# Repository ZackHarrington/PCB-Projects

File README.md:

# PCB Projects
This repository holds all my personal Autodesk Eagle (now Fusion 360 and KiCAD) projects and libraries

__Projects:__
- Billy Bass Board: 	A board to convert or 'hack' a Big Mouth Billy Bass into an IoT device - in progress
- Christmas Snow Globe:	A board using an ATtiny85 as a 6-hour timer IC in a custom snow globe - made as a gift
- Greek Keyboard:	A 5x6 key keyboard using an ATmega32u4 and HID to input Greek Unicode - made as a gift
- LED Test Board:	A simple board for testing any combination of LED, resistor, and power source
- USB UART Board:	Two small boards for programming ESP32 modules, each for a different USB-to-UART IC

__Libraries:__
- Aesthetics:	Silkscreen and copper designs
- Capacitors: 	SEM (Samsung Electro-Mechanics) MLCC capacitors
- Connectors: 	Board inputs or outputs
- Diodes:	Standard and Schottky diodes with Kingbright LEDs
- Energy:	Batteries and energy storage
- ICs: 		Integrates circuits
- Inductors:	SEM (Samsung Electro-Mechanics) Power Inductors
- Oscillators:	Crystal Oscillators
- Resistors:	SEM (Samsung Electro-Mechanics) CHIP-R chip resistors and potentiometers
- Switches: 	Physical buttons and switches
- Symbols:	Schematic symbols
- Transistors:	Discrete MOSFETs and BJTs

__Design Blocks:__
- ESP32 Wrover Module:	All standard capacitors and connections for implementing an ESP32-WROVER module

Note: I'm still in the process of finalizing the documentation for each project

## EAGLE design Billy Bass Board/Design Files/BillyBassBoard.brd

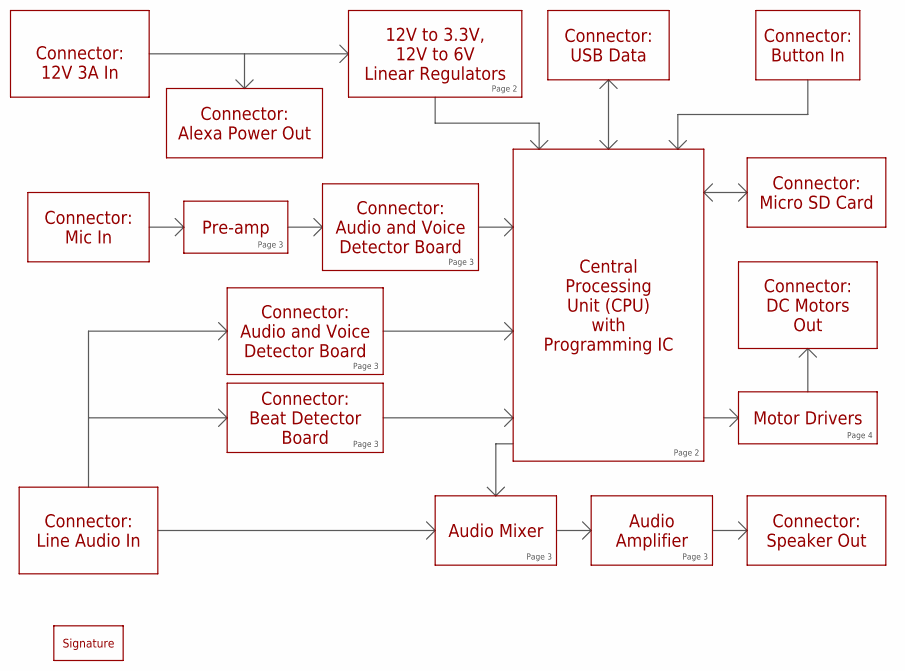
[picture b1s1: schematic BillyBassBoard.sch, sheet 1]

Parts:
U$122: SIGNATURE

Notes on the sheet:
Central Processing Unit (CPU) with Programming IC
Connector: 12V 3A In
Connector: Line Audio In
Connector: Speaker Out
Connector: DC Motors Out
12V to 3.3V, 12V to 6V Linear Regulators
Motor Drivers
Audio Mixer
Audio Amplifier
Page 2
Page 4
Page 3
Connector: Micro SD Card
Connector: Button In
Connector: USB Data
Connector: Alexa Power Out
Connector: Beat Detector Board
Connector: Audio and Voice Detector Board
Connector: Mic In
Pre-amp

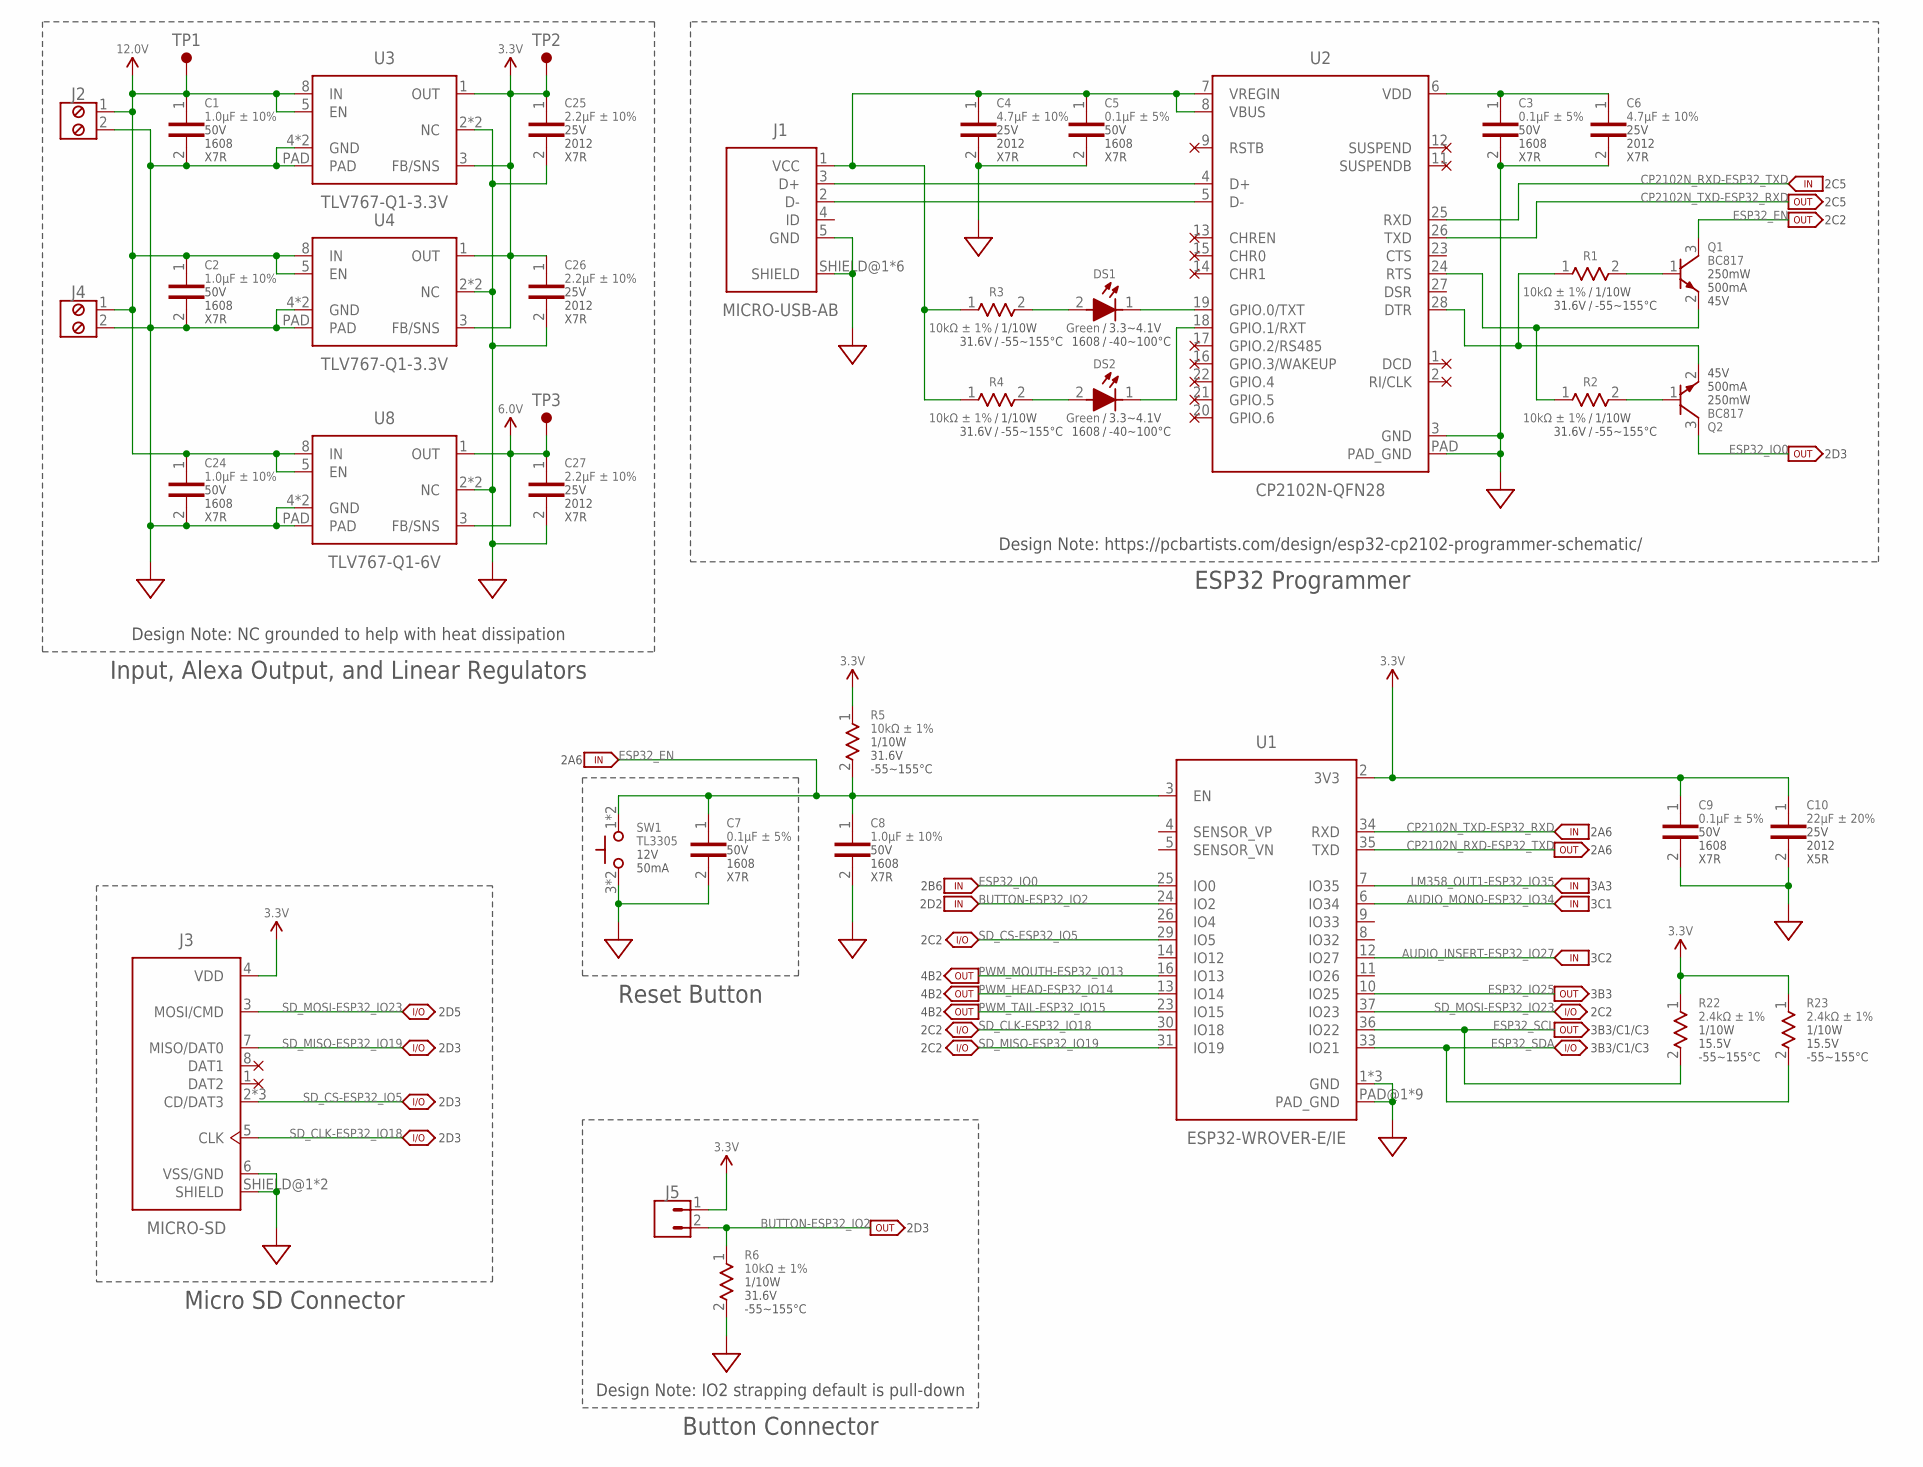
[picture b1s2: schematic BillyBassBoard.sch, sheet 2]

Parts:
C1, C2, C8, C24: 1.0µF ± 10%; 1608-SEM
C3, C5, C7, C9: 0.1µF ± 5%; 1608-SEM
C4, C6: 4.7µF ± 10%; 2012-SEM
C10: 22µF ± 20%; 2012-SEM
C25, C26, C27: 2.2µF ± 10%; 2012-SEM
DS1, DS2: Green; 1608
J1: MICRO-USB-AB; 47589-0001
J2, J4: MPT-2-SCREW; MPT-0.5/2-2.54
J3: MICRO-SD; MEM2061
J5: JST-XH-2; B2B-XH-A
Q1, Q2: BC817; SOT-23
R1, R2, R3, R4, R5, R6: 10kΩ ± 1%; 1608-SEM
R22, R23: 2.4kΩ ± 1%; 1608-SEM
SW1: TL3305
TP1, TP2, TP3: TEST-POINT
U1: ESP32-WROVER-E/IE
U2: CP2102N-QFN28; QFN28
U3, U4: TLV767-Q1-3.3V; VSON
U8: TLV767-Q1-6V; VSON

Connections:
3.3V: C9.1, C10.1, C25.1, C26.1, J3.4 (VDD), J5.1, R5.1, R22.1, R23.1, TP2.TP, U1.2 (3V3), U3.1 (OUT), U3.3 (FB/SNS), U4.1 (OUT), U4.3 (FB/SNS); also elsewhere on the board
6.0V: C27.1, TP3.TP, U8.1 (OUT), U8.3 (FB/SNS); also elsewhere on the board
12.0V: C1.1, C2.1, C24.1, J2.1, J4.1, TP1.TP, U3.5 (EN), U3.8 (IN), U4.5 (EN), U4.8 (IN), U8.5 (EN), U8.8 (IN)
AUDIO_INSERT-ESP32_IO27: U1.12 (IO27); also elsewhere on the board
AUDIO_MONO-ESP32_IO34: U1.6 (IO34); also elsewhere on the board
BUTTON-ESP32_IO2: J5.2, R6.1, U1.24 (IO2)
CP2102N_D+: J1.3 (D+), U2.4 (D+)
CP2102N_D-: J1.2 (D-), U2.5 (D-)
CP2102N_DTR: Q2.2 (E), R1.1, U2.28 (DTR)
CP2102N_RTS: Q1.2 (E), R2.1, U2.24 (RTS)
CP2102N_RXD-ESP32_TXD: U1.35 (TXD), U2.25 (RXD)
CP2102N_RXT: DS2.1, U2.18 (GPIO.1/RXT)
CP2102N_TXD-ESP32_RXD: U1.34 (RXD), U2.26 (TXD)
CP2102N_TXT: DS1.1, U2.19 (GPIO.0/TXT)
CP2102N_VBUS: C4.1, C5.1, J1.1 (VCC), R3.1, R4.1, U2.7 (VREGIN), U2.8 (VBUS)
CP2102N_VDD: C3.1, C6.1, U2.6 (VDD)
ESP32_EN: C7.1, C8.1, Q1.3 (C), R5.2, SW1.1 (2), SW1.2, U1.3 (EN)
ESP32_IO0: Q2.3 (C), U1.25 (IO0)
ESP32_IO25: U1.10 (IO25); also elsewhere on the board
ESP32_SCL: R22.2, U1.36 (IO22); also elsewhere on the board
ESP32_SDA: R23.2, U1.33 (IO21); also elsewhere on the board
GND: C1.2, C2.2, C3.2, C4.2, C5.2, C6.2, C7.2, C8.2, C9.2, C10.2, C24.2, C25.2, C26.2, C27.2, J1.5 (GND), J1.SHIELD@1 (SHIELD), J1.SHIELD@2 (SHIELD), J1.SHIELD@3 (SHIELD), J1.SHIELD@4 (SHIELD), J1.SHIELD@5 (SHIELD), J1.SHIELD@6 (SHIELD), J2.2, J3.6 (VSS/GND), J3.SHIELD@1 (SHIELD), J3.SHIELD@2 (SHIELD), J4.2, R6.2, SW1.3 (1), SW1.4 (1), U1.1 (GND), U1.15 (GND), U1.38 (GND), U1.PAD@1 (PAD_GND), U1.PAD@2 (PAD_GND), U1.PAD@3 (PAD_GND), U1.PAD@4 (PAD_GND), U1.PAD@5 (PAD_GND), U1.PAD@6 (PAD_GND), U1.PAD@7 (PAD_GND), U1.PAD@8 (PAD_GND), U1.PAD@9 (PAD_GND), U2.3 (GND), U2.PAD (PAD_GND), U3.2 (NC), U3.4 (GND), U3.6 (GND), U3.7 (NC), U3.PAD, U4.2 (NC), U4.4 (GND), U4.6 (GND), U4.7 (NC), U4.PAD, U8.2 (NC), U8.4 (GND), U8.6 (GND), U8.7 (NC), U8.PAD; also elsewhere on the board
LM358_OUT1-ESP32_IO35: U1.7 (IO35); also elsewhere on the board
unnamed: Q1.1 (B), R1.2
unnamed: Q2.1 (B), R2.2
unnamed: DS1.2, R3.2
unnamed: DS2.2, R4.2
PWM_HEAD-ESP32_IO14: U1.13 (IO14)
PWM_MOUTH-ESP32_IO13: U1.16 (IO13)
PWM_TAIL-ESP32_IO15: U1.23 (IO15)
SD_CLK-ESP32_IO18: J3.5 (CLK), U1.30 (IO18)
SD_CS-ESP32_IO5: J3.2 (CD/DAT3), J3.CD@1 (CD/DAT3), J3.CD@2 (CD/DAT3), U1.29 (IO5)
SD_MISO-ESP32_IO19: J3.7 (MISO/DAT0), U1.31 (IO19)
SD_MOSI-ESP32_IO23: J3.3 (MOSI/CMD), U1.37 (IO23)

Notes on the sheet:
Input, Alexa Output, and Linear Regulators
Design Note: https://pcbartists.com/design/esp32-cp2102-programmer-schematic/
ESP32 Programmer
Reset Button
2D5
2D3
2C2
2C5
Micro SD Connector
Button Connector
Design Note: IO2 strapping default is pull-down
2A6
2B6
2D2
3B3/C1/C3
3A3
3C1
3B3
4B2
Design Note: NC grounded to help with heat dissipation
3C2

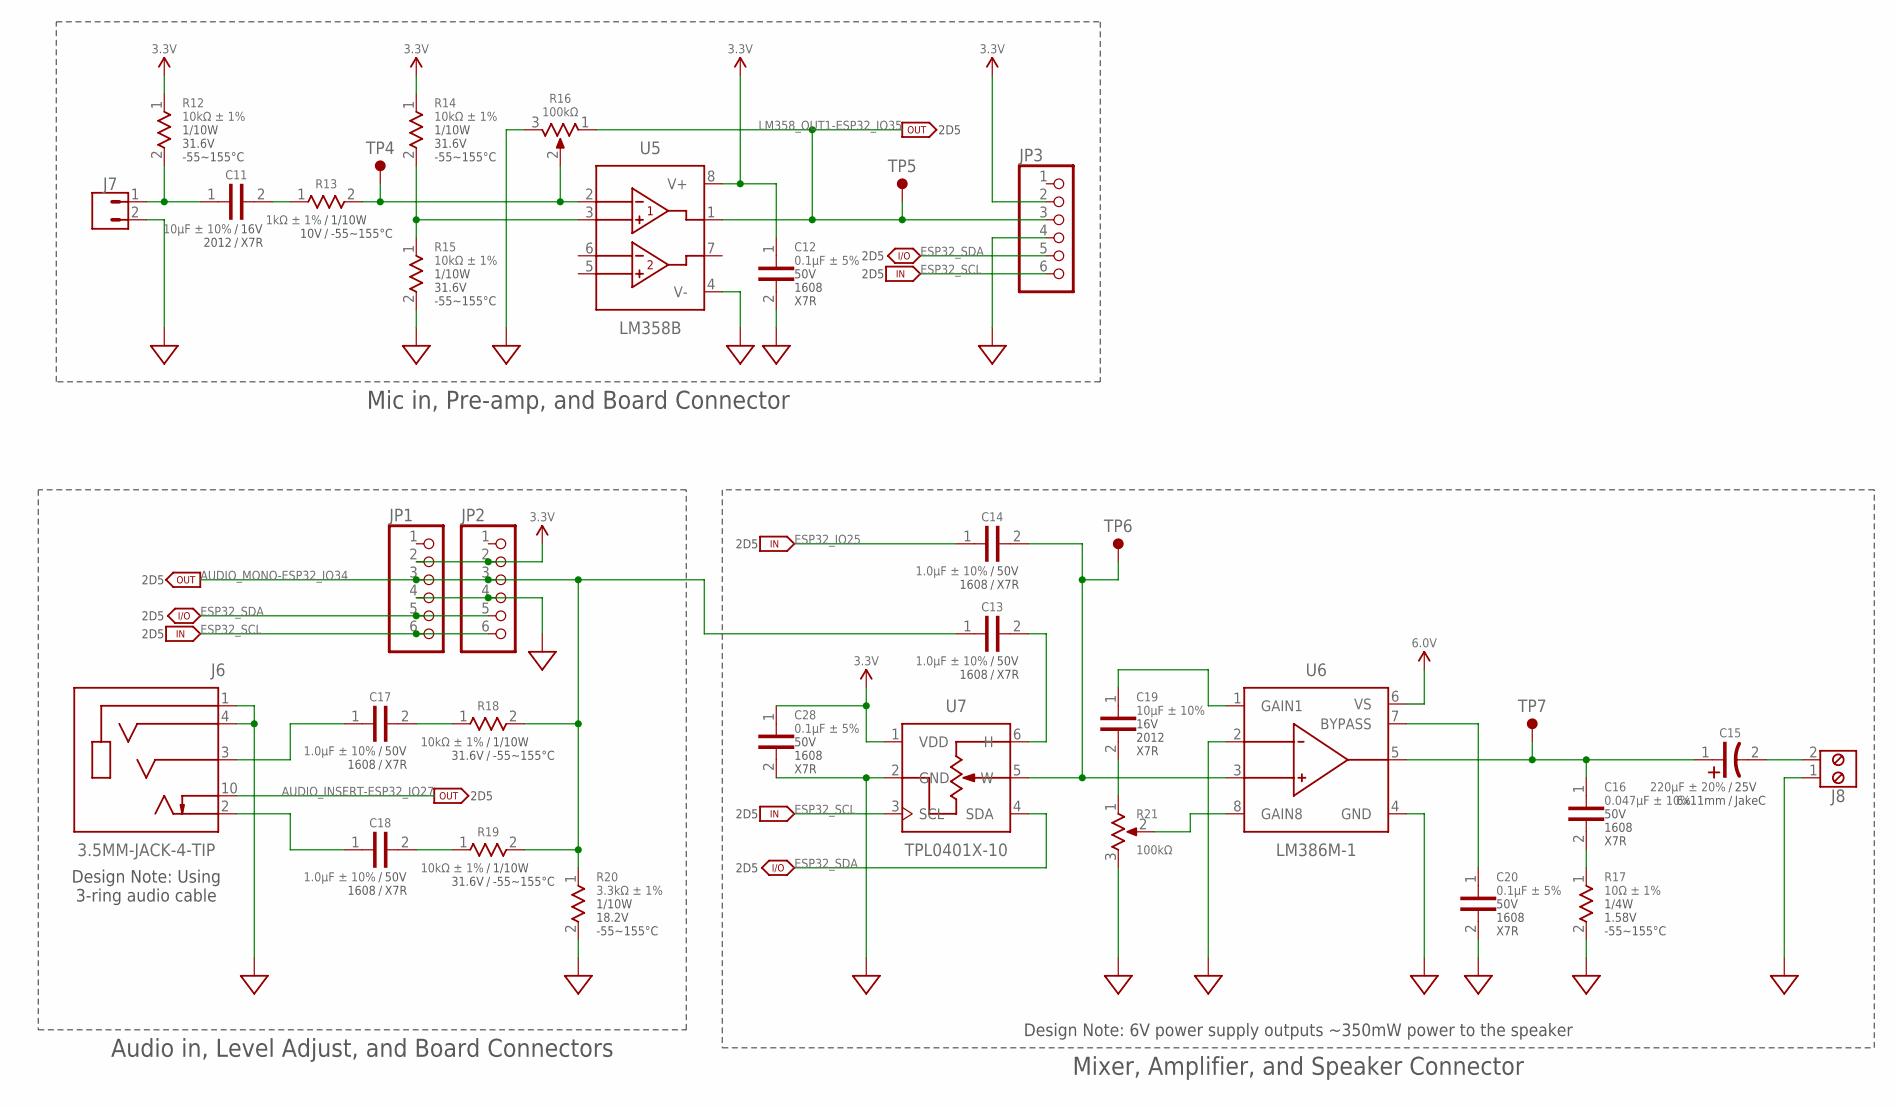
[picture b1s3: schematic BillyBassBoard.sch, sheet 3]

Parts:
C11, C19: 10µF ± 10%; 2012-SEM
C12, C20, C28: 0.1µF ± 5%; 1608-SEM
C13, C14, C17, C18: 1.0µF ± 10%; 1608-SEM
C15: 220µF ± 20%; 6X11-E-FLAT-REV
C16: 0.047µF ± 10%; 1608-SEM
J6: 3.5MM-JACK-4-TIP; SJ2-358940-SMT
J7: JST-XH-2; B2B-XH-A
J8: MPT-2-SCREW; MPT-0.5/2-2.54
JP1, JP2, JP3: PINHD-1X6; 1X06
R12, R14, R15, R18, R19: 10kΩ ± 1%; 1608-SEM
R13: 1kΩ ± 1%; 1608-SEM
R16, R21: 100kΩ; 3314J
R17: 10Ω ± 1%; 3216-SEM
R20: 3.3kΩ ± 1%; 1608-SEM
TP4, TP5, TP6, TP7: TEST-POINT
U5: LM358B; D0008A-SOIC
U6: LM386M-1; D0008A-SOIC
U7: TPL0401X-10; SC70

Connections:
3.3V: C12.1, C28.1, JP1.2, JP2.2, JP3.2, R12.1, R14.1, U5.8 (V+), U7.1 (VDD); also elsewhere on the board
6.0V: U6.6 (VS); also elsewhere on the board
AUDIO_INSERT-ESP32_IO27: J6.10 (TIP_SWITCH); also elsewhere on the board
AUDIO_LEFT: C18.1, J6.2 (TIP)
AUDIO_MONO-ESP32_IO34: C13.1, JP1.3, JP2.3, R18.2, R19.2, R20.1; also elsewhere on the board
AUDIO_RIGHT: C17.1, J6.3 (RING_1)
ESP32_IO25: C14.1; also elsewhere on the board
ESP32_SCL: JP1.6, JP2.6, JP3.6, U7.3 (SCL); also elsewhere on the board
ESP32_SDA: JP1.5, JP2.5, JP3.5, U7.4 (SDA); also elsewhere on the board
GND: C12.2, C20.2, C28.2, J6.1 (SLEEVE), J6.4 (RING_2), J7.2, J8.1, JP1.4, JP2.4, JP3.4, R15.2, R16.3, R17.2, R20.2, R21.3, U5.4 (V-), U6.2 (-INPUT), U6.4 (GND), U7.2 (GND); also elsewhere on the board
LM358_IN1+: R14.2, R15.1, U5.3 (IN1+)
LM358_IN1-: R13.2, R16.2, TP4.TP, U5.2 (IN1-)
LM358_OUT1-ESP32_IO35: JP3.3, R16.1, TP5.TP, U5.1 (OUT1); also elsewhere on the board
LM386M-G1: C19.1, U6.1 (GAIN1)
LM386M_BYPASS: C20.1, U6.7 (BYPASS)
LM386M_G8: R21.2, U6.8 (GAIN8)
LM386M_IN+: C14.2, TP6.TP, U6.3 (+INPUT), U7.5 (W)
LM386M_OUT: C15.1, C16.1, TP7.TP, U6.5 (VOUT)
MIC+: C11.1, J7.1, R12.2
unnamed: C11.2, R13.1
unnamed: C16.2, R17.1
unnamed: C17.2, R18.1
unnamed: C18.2, R19.1
unnamed: C19.2, R21.1
SPEAKER+: C15.2, J8.2
TPL0401_H: C13.2, U7.6 (H)

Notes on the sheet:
Design Note: Using 3-ring audio cable
Mic in, Pre-amp, and Board Connector
Mixer, Amplifier, and Speaker Connector
Audio in, Level Adjust, and Board Connectors
2D5
Design Note: 6V power supply outputs ~350mW power to the speaker

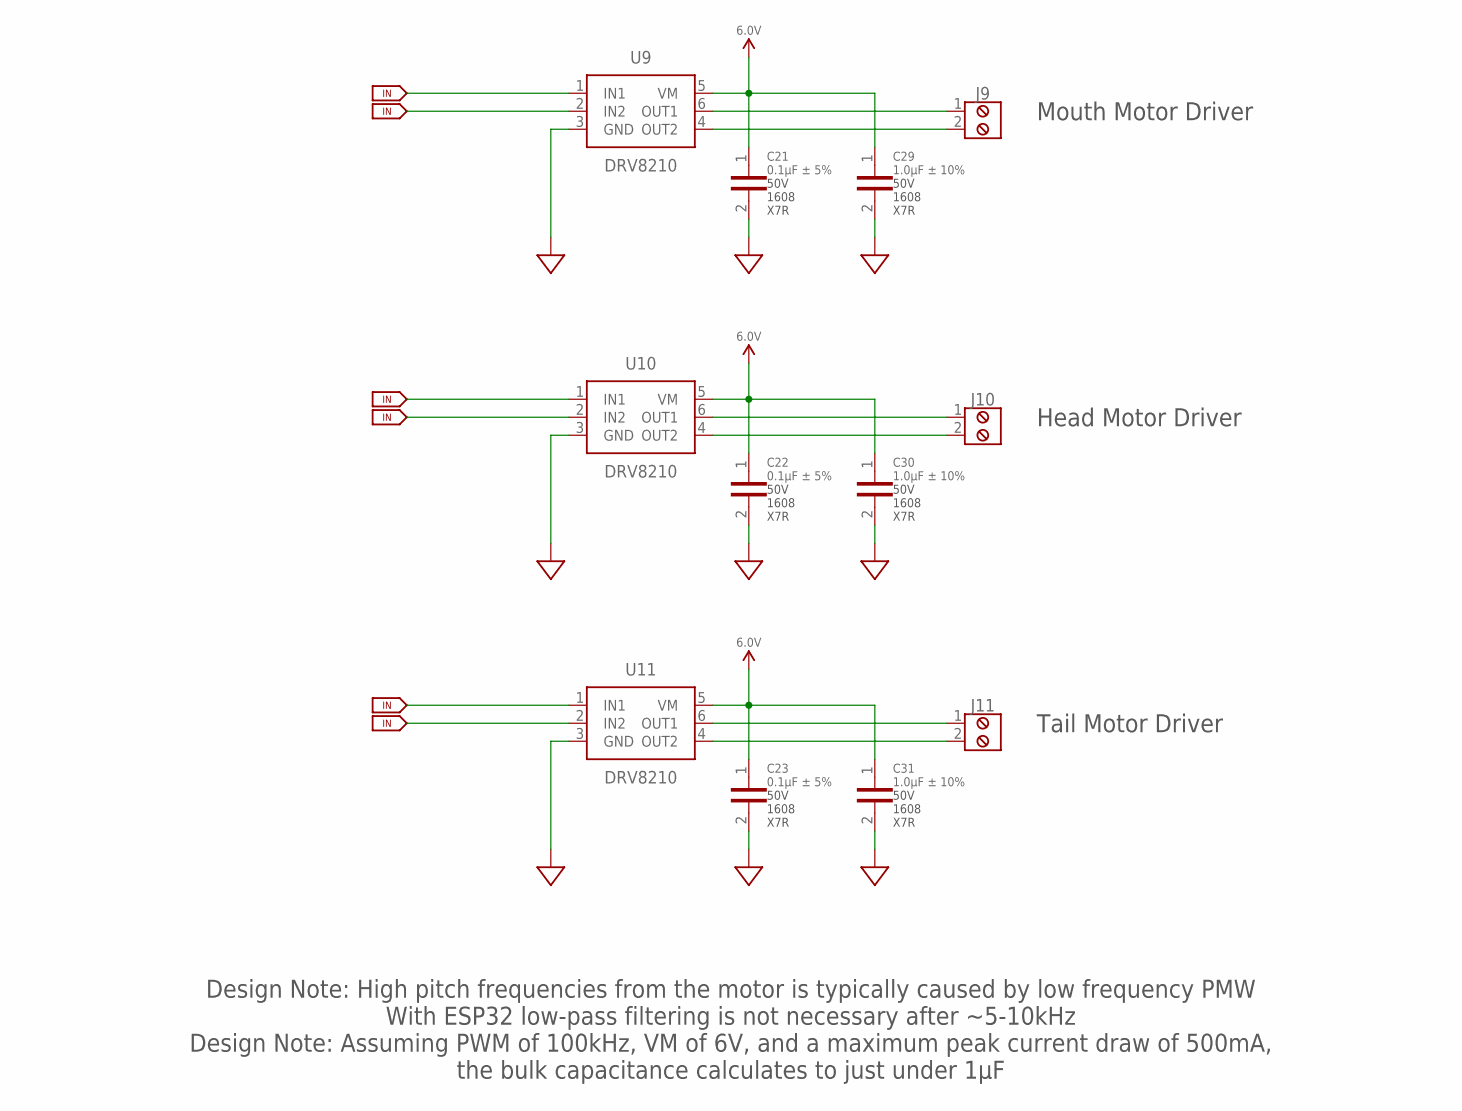
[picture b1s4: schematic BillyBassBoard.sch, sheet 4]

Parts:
C21, C22, C23: 0.1µF ± 5%; 1608-SEM
C29, C30, C31: 1.0µF ± 10%; 1608-SEM
J9, J10, J11: MPT-2-SCREW; MPT-0.5/2-2.54
U9, U10, U11: DRV8210; SOT563

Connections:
6.0V: C21.1, C22.1, C23.1, C29.1, C30.1, C31.1, U9.5 (VM), U10.5 (VM), U11.5 (VM); also elsewhere on the board
DRV82101_OUT1: J9.1, U9.6 (OUT1)
DRV82101_OUT2: J9.2, U9.4 (OUT2)
DRV82102_OUT1: J10.1, U10.6 (OUT1)
DRV82102_OUT2: J10.2, U10.4 (OUT2)
DRV82103_OUT1: J11.1, U11.6 (OUT1)
DRV82103_OUT2: J11.2, U11.4 (OUT2)
GND: C21.2, C22.2, C23.2, C29.2, C30.2, C31.2, U9.3 (GND), U10.3 (GND), U11.3 (GND); also elsewhere on the board

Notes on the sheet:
Design Note: High pitch frequencies from the motor is typically caused by low frequency PMW With ESP32 low-pass filtering is not necessary after ~5-10kHz Design Note: Assuming PWM of 100kHz, VM of 6V, and a maximum peak current draw of 500mA, the bulk capacitance calculates to just under 1µF
Mouth Motor Driver
Head Motor Driver
Tail Motor Driver

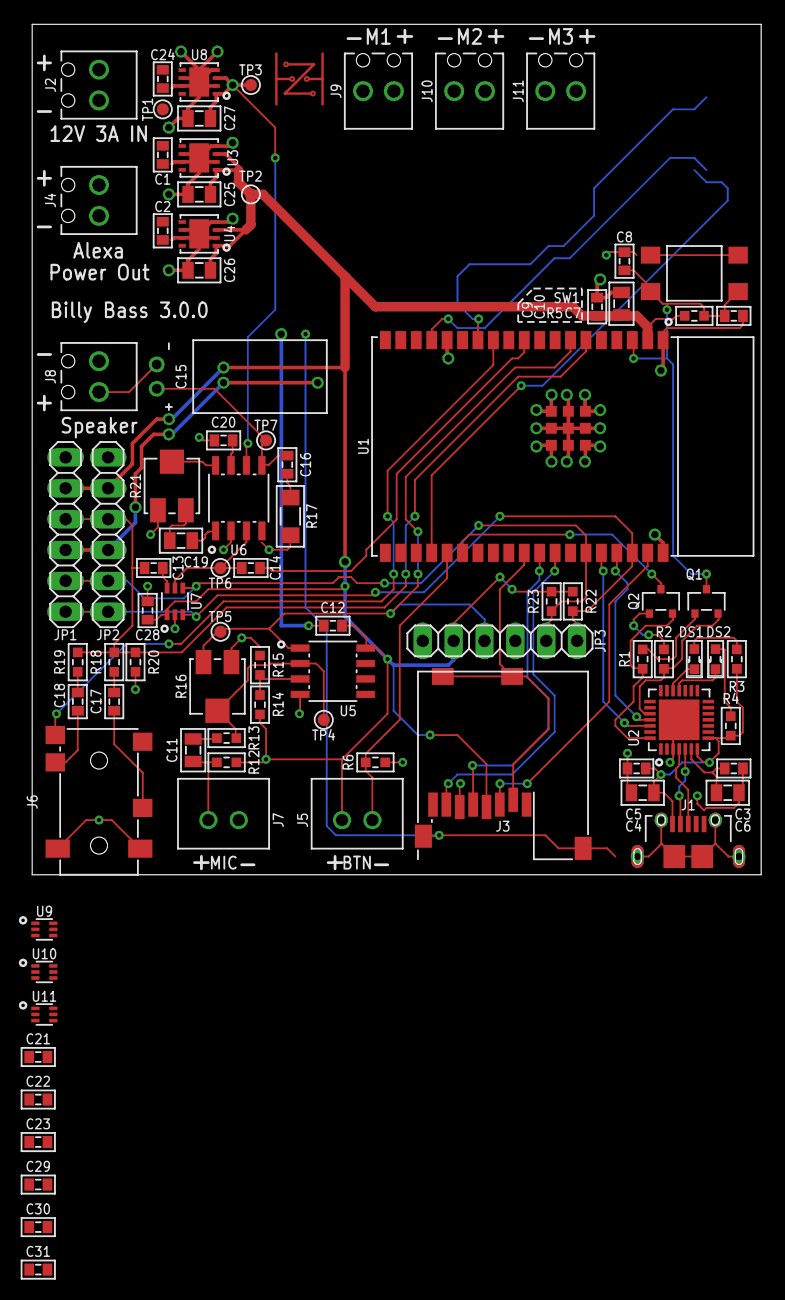
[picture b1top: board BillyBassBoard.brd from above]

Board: 2 copper layers, 60.0 x 70.0 mm, 87 parts (0 on the bottom side), 54 nets.

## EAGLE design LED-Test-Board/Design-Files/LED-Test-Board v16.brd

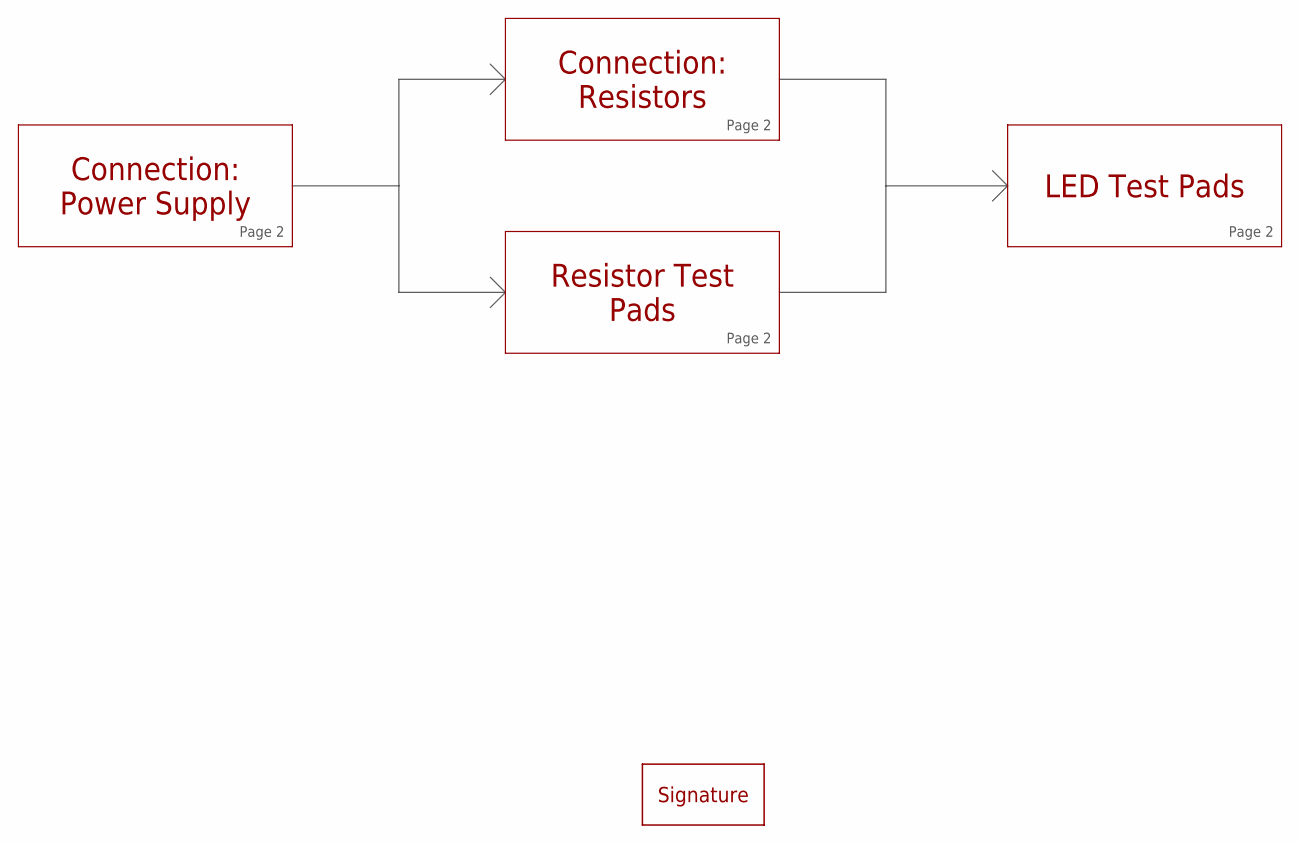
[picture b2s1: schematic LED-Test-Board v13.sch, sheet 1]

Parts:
U$5: SIGNATURE

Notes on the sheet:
Connection: Power Supply
Connection: Resistors
LED Test Pads
Resistor Test Pads
Page 2

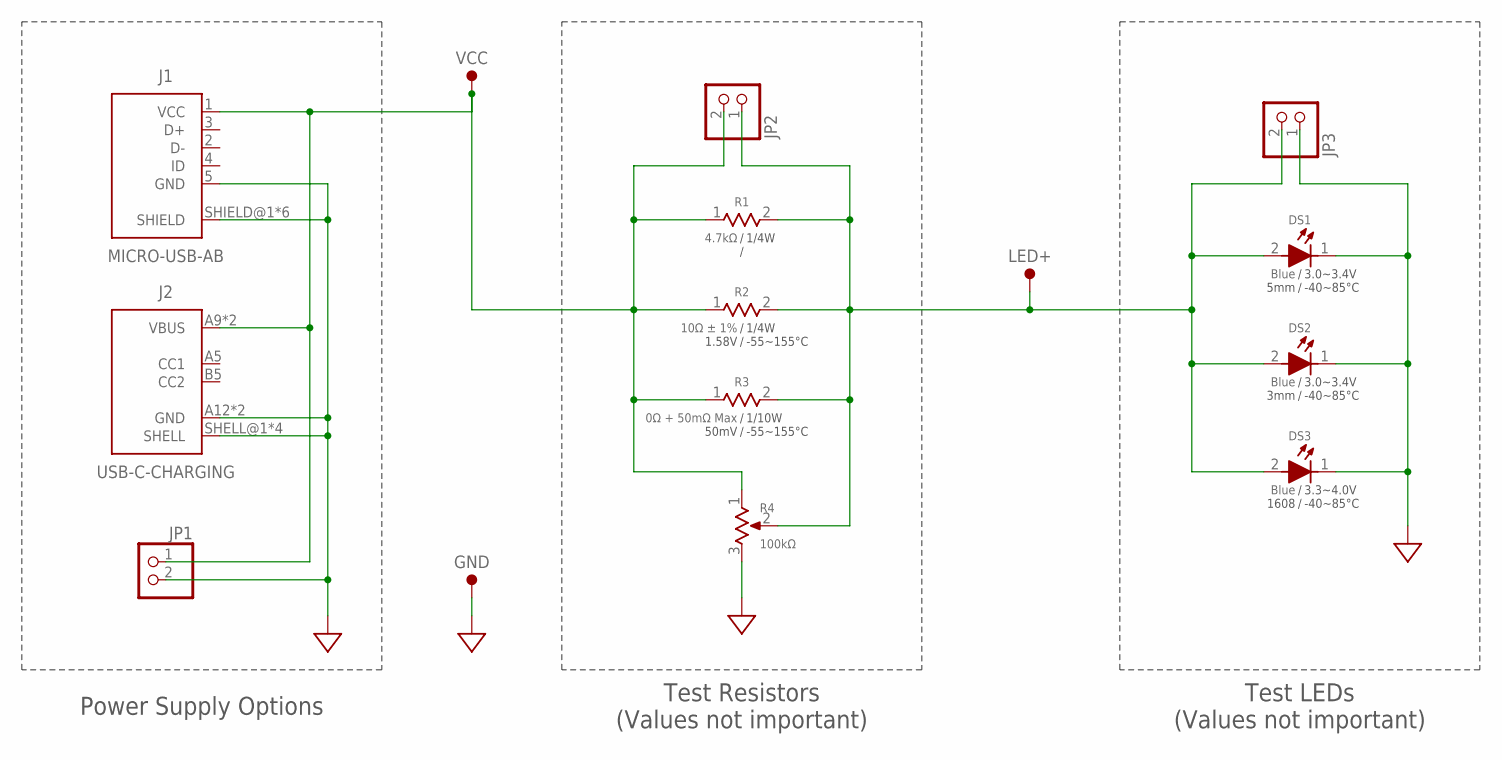
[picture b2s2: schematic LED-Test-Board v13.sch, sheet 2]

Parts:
DS1: Blue; 5MM-TH
DS2: Blue; 3MM-TH
DS3: Blue; 1608
GND: TEST-POINT
J1: MICRO-USB-AB; 47589-0001
J2: USB-C-CHARGING; USB-4125
JP1, JP2, JP3: PINHD-1X2; 1X02
LED+: TEST-POINT
R1: 4.7kΩ; 1/4W-TH
R2: 10Ω ± 1%; 3216-SEM
R3: 0Ω + 50mΩ Max; 1608-SEM
R4: 100kΩ; 3314J
VCC: TEST-POINT

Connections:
GND: DS1.1, DS2.1, DS3.1, GND.TP, J1.5 (GND), J1.SHIELD@1 (SHIELD), J1.SHIELD@2 (SHIELD), J1.SHIELD@3 (SHIELD), J1.SHIELD@4 (SHIELD), J1.SHIELD@5 (SHIELD), J1.SHIELD@6 (SHIELD), J2.A12 (GND), J2.B12 (GND), J2.SHELL@1 (SHELL), J2.SHELL@2 (SHELL), J2.SHELL@3 (SHELL), J2.SHELL@4 (SHELL), JP1.2, JP3.1, R4.3
RES_OUT: DS1.2, DS2.2, DS3.2, JP2.1, JP3.2, LED+.TP, R1.2, R2.2, R3.2, R4.2
VCC: J1.1 (VCC), J2.A9 (VBUS), J2.B9 (VBUS), JP1.1, JP2.2, R1.1, R2.1, R3.1, R4.1, VCC.TP

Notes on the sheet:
Test LEDs (Values not important)
Test Resistors (Values not important)
Power Supply Options

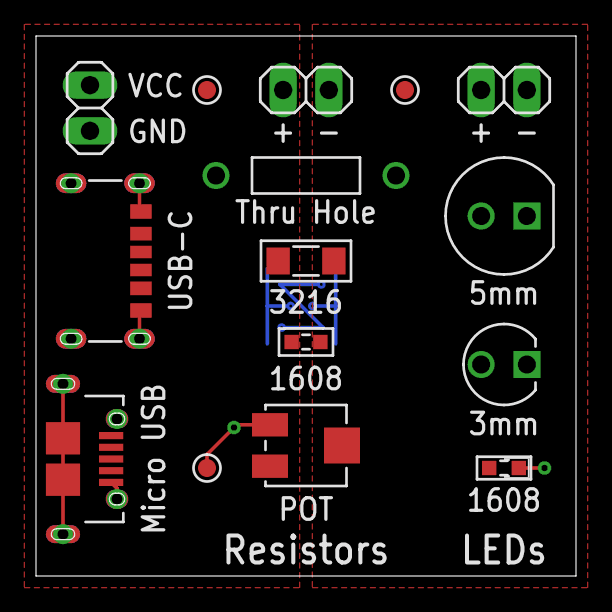
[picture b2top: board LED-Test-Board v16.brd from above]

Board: 2 copper layers, 30.0 x 30.0 mm, 16 parts (1 on the bottom side), 3 nets.

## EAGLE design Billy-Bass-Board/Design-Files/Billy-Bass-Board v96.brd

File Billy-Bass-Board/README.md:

# Billy Bass Board 

Over the course of this project, I have developed more and more sophisticated ways to 'hack' a Big Mouth Billy Bass into an IoT device. A few others have successfully done this to a reasonable degree; however, I continue to use this as an educational challenge and hope to address some of the shortcomings I've seen in other attempts. These include inaccurate motor timing and building a standalone device capable of voice recognition without internet access.

## Latest Version: v3.0.0

This latest version attempts to transition away from the Amazon Echo Dot into a completely standalone device. This includes adding an on-board I2S ADC and DAC, transitioning to H-bridge motor drivers, and addressing the shortcoming of version two.

Note that while the board is complete, I am still completing programming and attempting to migrate version two's code from Arduino into the ESP_IDF framework.

## Features

The following sections explain the components and features of the lastest board, including their uses, my reasoning for including them, and how they contribute to the standalone capability of the device.

### ESP32-Wrover

This microprocessor has been my key to transitioning from the Amazon Echo Dot to a standalone device. With a built-in Bluetooth and Wi-Fi antenna, I can now connect directly to the microprocessor from my phone and from the microprocessor to the internet. Additionally, the ESP32 can interface with the Arduino ecosystem and libraries, including sophisticated ones like pschatzmann's Audio Tools.

### I2S ADC and DAC

In the quest for better reliability and sound quality, I found the newly added I2S ADC and DAC. These enable me to quickly and accurately stream sound in and out without compromising signal integrity. Furthermore, audio can now be fully controlled and converted on-board, adding the final piece of the standalone device.

### H-Bridge Motor Drivers

H-bridge motor driver ICs have been added to reduce size, increase efficiency, and boost the control over each motor. Now, forward and backward movement can be controlled through software and fully coupled to the audio signals. 

### Connectors

New:
- Touch Sensors - For volume control, removing a dependency on the Echo Dot
- External Switch - For hardware toggling of motor movements

Still Supported:
- Speaker
- Aux Audio Jack
- Microphone
- Button
- SD Card
- 3 Motors
- 12V Out

## Image Gallery (v3.0.0)

Below are some renders and images of the latest version of the board and Billy.

Full 3D PCB render of v3.0.0.

Comparison between the size and signal routing of v2.0.0 and v3.0.0

0402 (1005) sized capacitors, my thumb for reference. This was my first experience using components this small.

Close up of the I2S ADC in the rendered 3D PCB.

Similar angle showing most of the soldered board.

## Version History

The following is a reverse-chronological list of past versions. Note that the version numbers reference the hardware and PCB updates rather than the software changes.

- v3.0.0 (Fall 2023 - Spring 2024)
  - Added external I2S ADCs and DACs for more accurate readings and audio playback from the ESP32
  - Added a pre-amp to the aux audio input for larger amplitude, noise-free readings
  - Fixed grounding issues by transitioning to a single ground plane and controlling return currents
  - Added connectors for touch sensors and an external switch
  - Added a power indictor LED 
  - Removed the programming circuitry in favor of cost savings and utilizing the USB-UART boards
  - Transitioned from the I2C digipot to an audio mute circuit
  - Switched to H-bridge motor drivers for more control and flexibility

- v2.0.0 (Fall 2022 - Summer 2023)
  - Transitioned all the hardware and circuit designs to a PCB, including the audio amplifier, microprocessor, voltage regulators, and connectors
  - Added a programming circuit onto the PCB for a single point connection
  - Added connectors interfacing the PCB and Amazon Echo Dot
  - Developed crude unidirectional motor drivers with PWM controlled NPN transistors
  - Added an I2C digipot for volume control
  - Expanded upon the audio processing code
  - Added an SD card slot for custom audio files

- v1.0.0 (Summer 2022)
  - Initial attempt at converting the Big Mouth Billy Bass into an IoT device
  - Utilized an Arduino Uno with a motor driver shield for motor control
  - Deconstructed an Amazon Echo Dot and wired the output audio into the Arduino
  - Located a test point on the Amazon board that is pulled high when the wake word is detected
  - Created very crude code to move the mouth when audio was detected
  - Coded the head to move when the wake word was detected

## License

This project is still in the development stage with many flaws and much room for improvement. Should you be interested in using it, I would recommend reading the considerations below and adjusting the design to fit your needs.

## Project Considerations and Future Work

The following are considerations for others and ideas for what to change in future versions.
- The I2S SCLK, LRCLK, and motor driver pinheads simply act as antennas if soldered on and generate unnecessary noise
- Noise and interference is still being output by the speaker when no audio is output, consider other output capacitance options

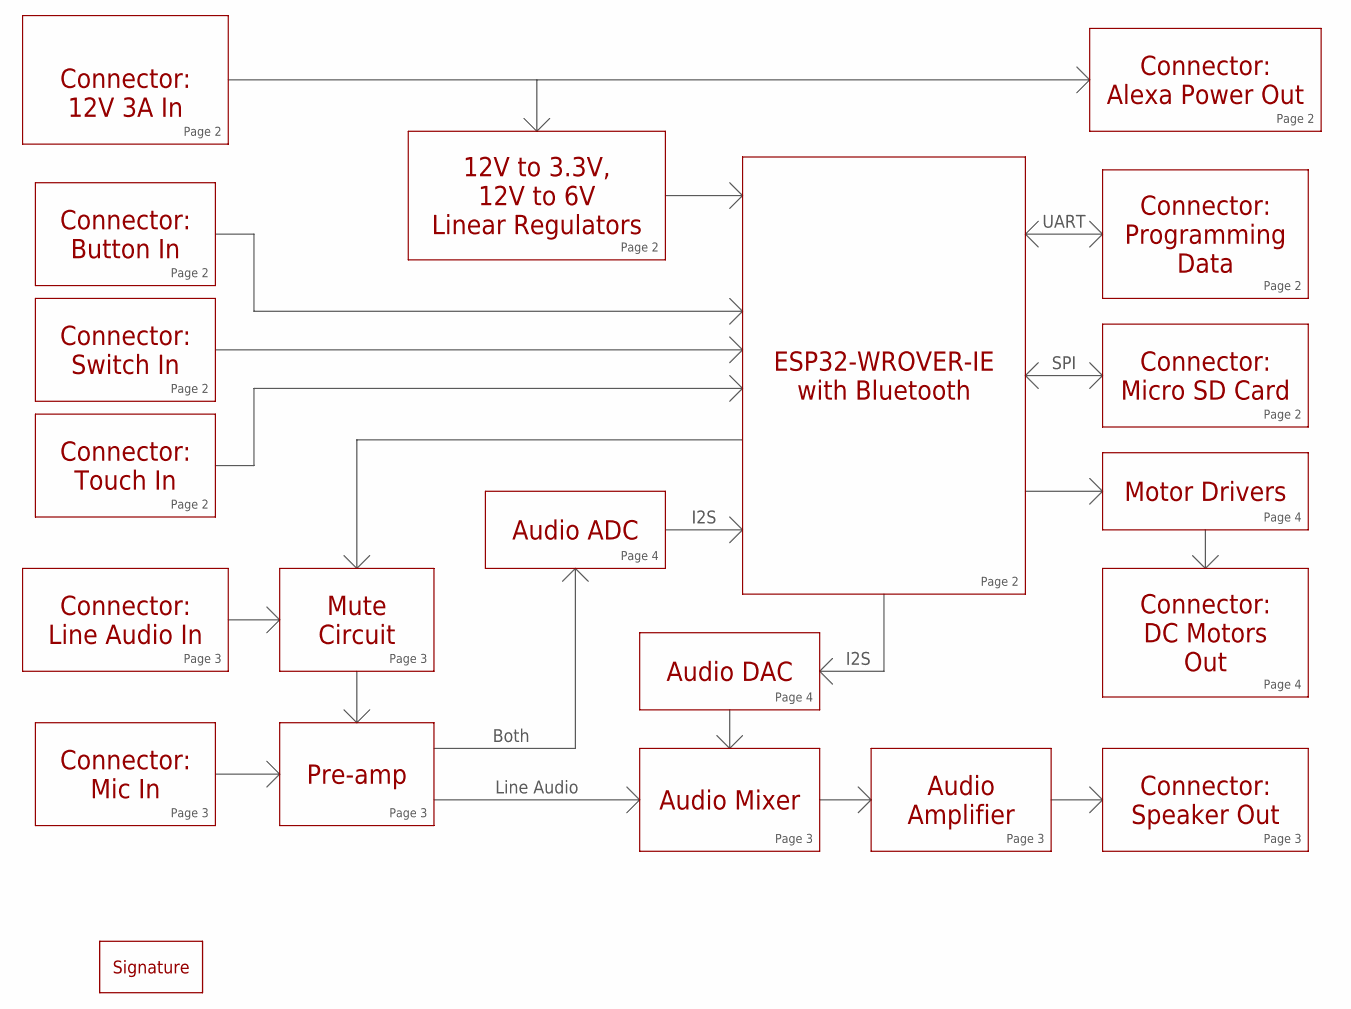
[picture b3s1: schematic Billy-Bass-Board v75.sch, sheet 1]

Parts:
U$122: SIGNATURE

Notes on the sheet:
ESP32-WROVER-IE with Bluetooth
Connector: 12V 3A In
Connector: Line Audio In
Connector: Speaker Out
Connector: DC Motors Out
12V to 3.3V, 12V to 6V Linear Regulators
Motor Drivers
Audio Mixer
Audio Amplifier
Page 2
Page 4
Page 3
Connector: Micro SD Card
Connector: Programming Data
Connector: Alexa Power Out
Connector: Mic In
Pre-amp
Connector: Touch In
Connector: Switch In
Connector: Button In
Audio DAC
Audio ADC
UART
SPI
I2S
Mute Circuit
Line Audio
Both
